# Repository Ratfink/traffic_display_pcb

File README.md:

# traffic_display_pcb
PCB for the Traffic Signal LED Matrix Display.

## Licensing
This work is licensed under the Creative Commons Attribution-ShareAlike 4.0
International License. To view a copy of this license, visit
http://creativecommons.org/licenses/by-sa/4.0/ or send a letter to Creative
Commons, PO Box 1866, Mountain View, CA 94042, USA.

Around half of the schematic is heavily based on the [Adafruit Feather ESP8266
HUZZAH](https://github.com/adafruit/Adafruit-Feather-ESP8266-HUZZAH-PCB).
Although Adafruit seems to have forgotten to include the exact version of the
Creative Commons Attribution-ShareAlike license used (at the time of writing),
and this project is not really a redistribution of theirs, I will include their
text as requested to try to avoid treading on any legal toes.

### Adafruit-Feather-ESP8266-HUZZAH-PCB

PCB files for the Adafruit Feather ESP8266 HUZZAH

Format is EagleCAD schematic and board layout

For more details, check out the product page at

* https://www.adafruit.com/product/2821

Adafruit invests time and resources providing this open source design, please
support Adafruit and open-source hardware by purchasing products from Adafruit!

Designed by Adafruit Industries.  
Creative Commons Attribution, Share-Alike license, check license.txt for more
information All text above must be included in any redistribution

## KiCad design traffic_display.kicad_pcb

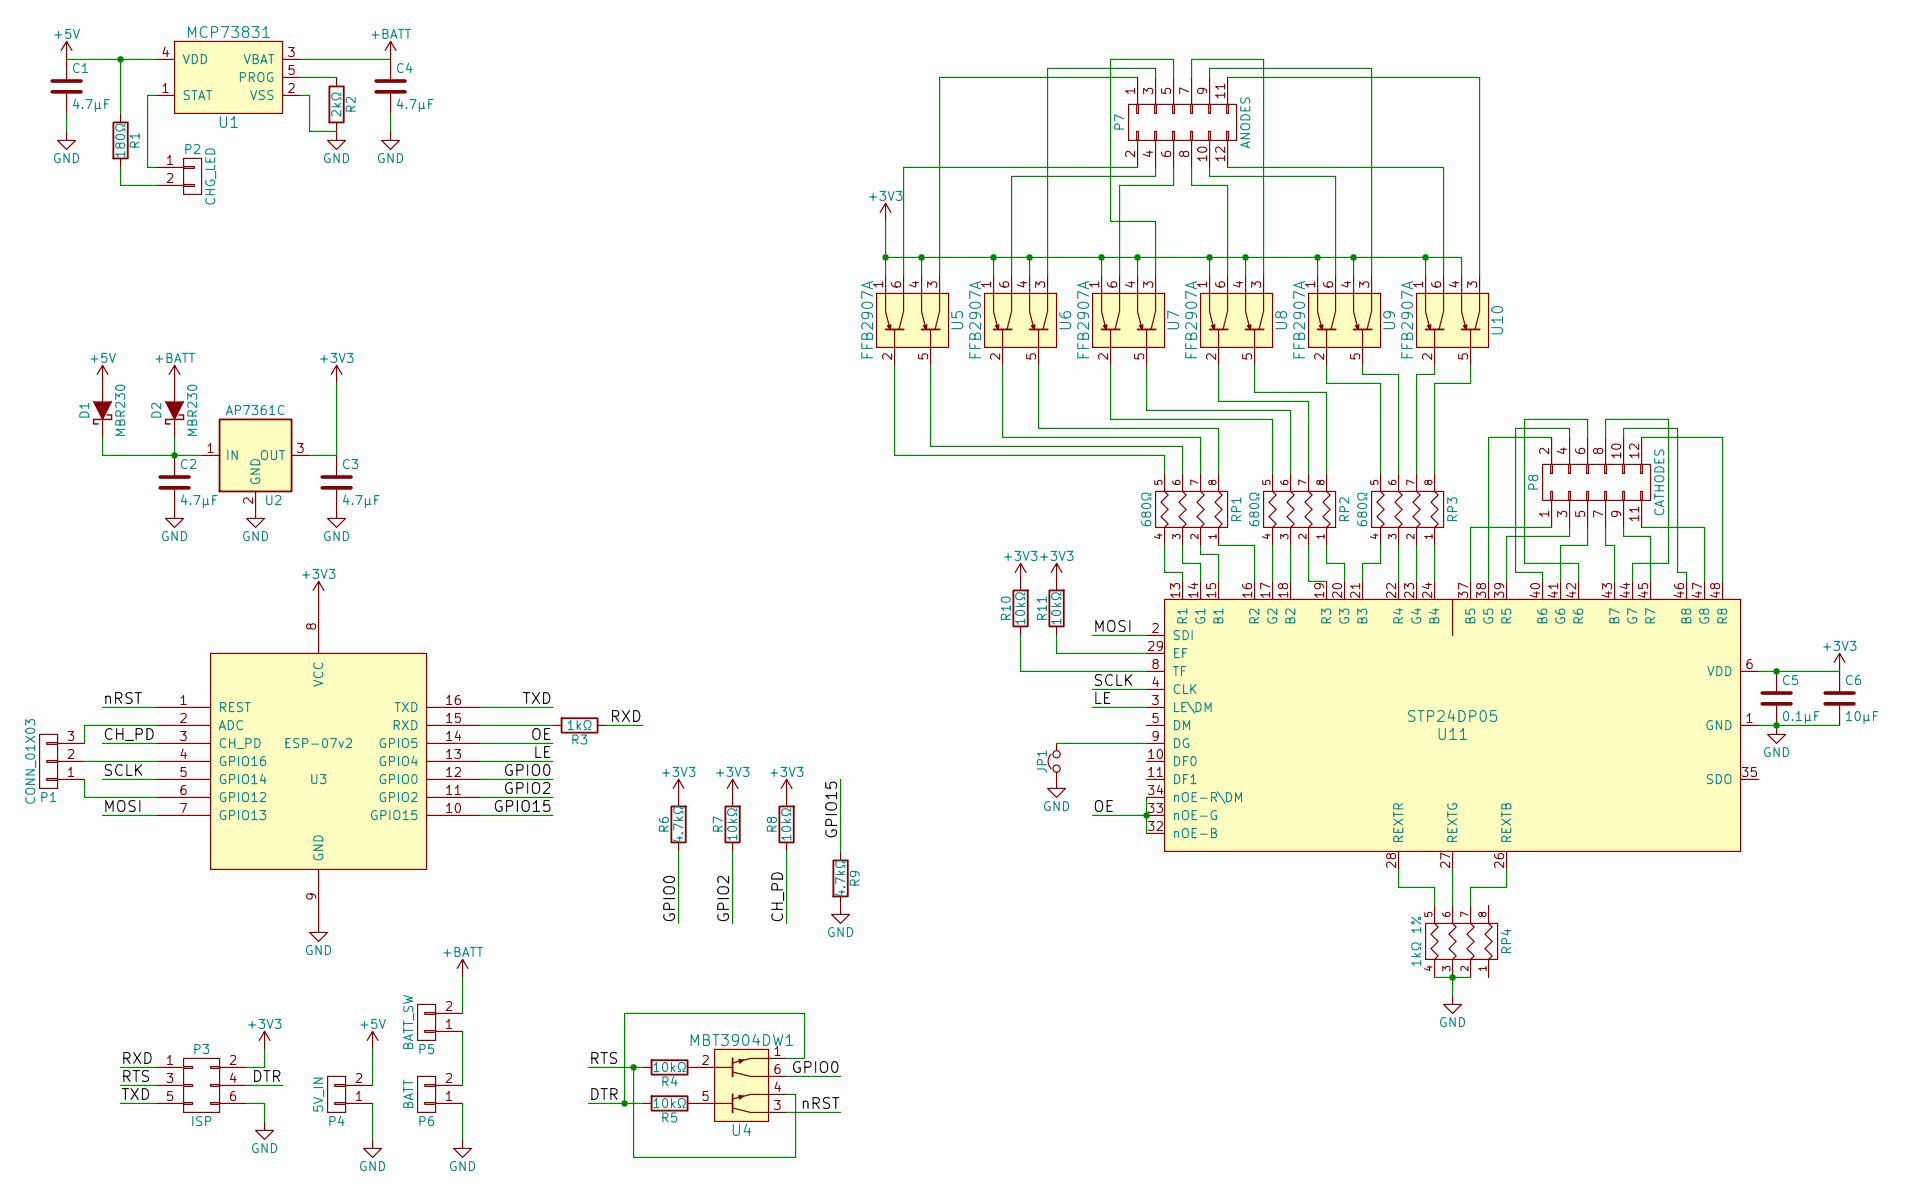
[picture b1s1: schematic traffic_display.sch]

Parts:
C1, C2, C3, C4: 4.7µF; C_0805_HandSoldering
C5: 0.1µF; C_0805_HandSoldering
C6: 10µF; C_0805_HandSoldering
D1, D2: MBR230; SOD-123
JP1: Jumper_NC_Small; R_0805_HandSoldering
P1: CONN_01X03; Pin_Header_Straight_1x03
P2: CHG_LED; Molex_KK-6410-02_02x2.54mm_Straight
P3: ISP; Pin_Header_Straight_2x03
P4: 5V_IN; Molex_KK-6410-02_02x2.54mm_Straight
P5: BATT_SW; Molex_KK-6410-02_02x2.54mm_Straight
P6: BATT; Molex_KK-6410-02_02x2.54mm_Straight
P7: ANODES; Pin_Header_Straight_2x06
P8: CATHODES; Pin_Header_Straight_2x06
R1: 180Ω; R_0805_HandSoldering
R2: 2kΩ; R_0805_HandSoldering
R3: 1kΩ; R_0805_HandSoldering
R4, R5, R7, R8, R10, R11: 10kΩ; R_0805_HandSoldering
R6, R9: 4.7kΩ; R_0805_HandSoldering
RP1, RP2, RP3: 680Ω; R_Array_Concave_4x0603
RP4: 1kΩ 1%; R_Array_Concave_4x0603
U1: MCP73831; SOT-23-5
U2: AP7361C; SOT-223
U3: ESP-07v2
U4: MBT3904DW1; SC-70-6_Handsoldering
U5, U6, U7, U8, U9, U10: FFB2907A; SC-70-6_Handsoldering
U11: STP24DP05; TQFP-48-1EP_7x7mm_Pitch0.5mm

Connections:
+3V3: C3.1, C5.1, C6.1, P3.2, R6.2, R7.2, R8.2, R10.2, R11.2, U2.3 (OUT), U3.8 (VCC), U5.1 (E1), U5.4 (E2), U6.1 (E1), U6.4 (E2), U7.1 (E1), U7.4 (E2), U8.1 (E1), U8.4 (E2), U9.1 (E1), U9.4 (E2), U10.1 (E1), U10.4 (E2), U11.6 (VDD), U11.31 (VDD)
+5V: C1.1, D1.2 (A), P4.2, R1.1, U1.4 (VDD)
+BATT: C4.1, D2.2 (A), P5.2, U1.3 (VBAT)
/CH_PD: R8.1, U3.3 (CH_PD)
/DTR: P3.4, R5.2, U4.1 (E1)
/GPIO0: R6.1, U3.12 (GPIO0), U4.6 (C1)
/GPIO2: R7.1, U3.11 (GPIO2)
/GPIO15: R9.1, U3.10 (GPIO15)
/LE: U3.13 (GPIO4), U11.3 (LE\DM)
/MOSI: U3.7 (GPIO13), U11.2 (SDI)
/OE: U3.14 (GPIO5), U11.32 (nOE-B), U11.33 (nOE-G), U11.34 (nOE-R\DM)
/RTS: P3.3, R4.2, U4.4 (E2)
/RXD: P3.1, R3.1
/SCLK: U3.5 (GPIO14), U11.4 (CLK)
/TXD: P3.5, U3.16 (TXD)
/nRST: U3.1 (REST), U4.3 (C2)
GND: C1.2, C2.2, C3.2, C4.2, C5.2, C6.2, JP1.1, P3.6, P4.1, P6.1, R2.2, R9.2, RP4.2, RP4.3, RP4.4, U1.2 (VSS), U2.2 (GND), U3.9 (GND), U11.1 (GND), U11.7 (GND), U11.12 (GND), U11.25 (GND), U11.30 (GND), U11.36 (GND), U11.49 (GND)
unnamed: C2.1, D1.1 (K), D2.1 (K), U2.1 (IN)
unnamed: JP1.2, U11.9 (DG)
unnamed: P1.1, U3.6 (GPIO12)
unnamed: P1.2, U3.4 (GPIO16)
unnamed: P1.3, U3.2 (ADC)
unnamed: P2.1, U1.1 (STAT)
unnamed: P2.2, R1.2
unnamed: P5.1, P6.2
unnamed: P7.1, U5.3 (C2)
unnamed: P7.2, U5.6 (C1)
unnamed: P7.3, U6.3 (C2)
unnamed: P7.4, U6.6 (C1)
unnamed: P7.5, U7.3 (C2)
unnamed: P7.6, U7.6 (C1)
unnamed: P7.7, U8.3 (C2)
unnamed: P7.8, U8.6 (C1)
unnamed: P7.9, U9.3 (C2)
unnamed: P7.10, U9.6 (C1)
unnamed: P7.11, U10.3 (C2)
unnamed: P7.12, U10.6 (C1)
unnamed: P8.1, U11.37 (B5)
unnamed: P8.2, U11.38 (G5)
unnamed: P8.3, U11.39 (R5)
unnamed: P8.4, U11.40 (B6)
unnamed: P8.5, U11.41 (G6)
unnamed: P8.6, U11.42 (R6)
unnamed: P8.7, U11.43 (B7)
unnamed: P8.8, U11.44 (G7)
unnamed: P8.9, U11.45 (R7)
unnamed: P8.10, U11.46 (B8)
unnamed: P8.11, U11.47 (G8)
unnamed: P8.12, U11.48 (R8)
unnamed: R2.1, U1.5 (PROG)
unnamed: R3.2, U3.15 (RXD)
unnamed: R4.1, U4.2 (B1)
unnamed: R5.1, U4.5 (B2)
unnamed: R10.1, U11.8 (TF)
unnamed: R11.1, U11.29 (EF)
unnamed: RP1.1, U11.16 (R2)
unnamed: RP1.2, U11.15 (B1)
unnamed: RP1.3, U11.14 (G1)
unnamed: RP1.4, U11.13 (R1)
unnamed: RP1.5 (R4), U5.2 (B1)
unnamed: RP1.6 (R3), U5.5 (B2)
unnamed: RP1.7 (R2), U6.2 (B1)
unnamed: RP1.8 (R1), U6.5 (B2)
unnamed: RP2.1, U11.20 (G3)
unnamed: RP2.2, U11.19 (R3)
unnamed: RP2.3, U11.18 (B2)
unnamed: RP2.4, U11.17 (G2)
unnamed: RP2.5 (R4), U7.2 (B1)
unnamed: RP2.6 (R3), U7.5 (B2)
unnamed: RP2.7 (R2), U8.2 (B1)
unnamed: RP2.8 (R1), U8.5 (B2)
unnamed: RP3.1, U11.24 (B4)
unnamed: RP3.2, U11.23 (G4)
unnamed: RP3.3, U11.22 (R4)
unnamed: RP3.4, U11.21 (B3)
unnamed: RP3.5 (R4), U9.2 (B1)
unnamed: RP3.6 (R3), U9.5 (B2)
unnamed: RP3.7 (R2), U10.2 (B1)
unnamed: RP3.8 (R1), U10.5 (B2)
unnamed: RP4.5 (R4), U11.28 (REXTR)
unnamed: RP4.6 (R3), U11.27 (REXTG)
unnamed: RP4.7 (R2), U11.26 (REXTB)

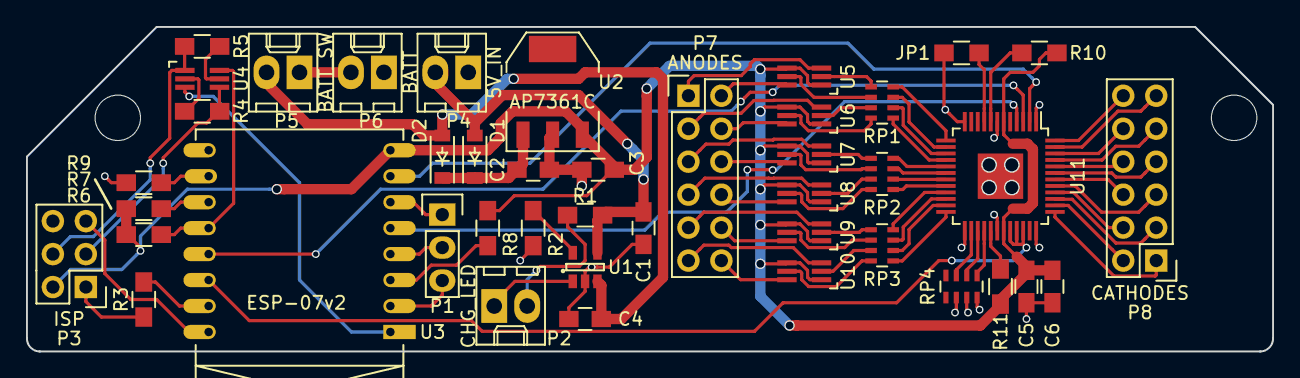
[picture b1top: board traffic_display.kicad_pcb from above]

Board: 2 copper layers, 96.0 x 25.0 mm, 43 parts (0 on the bottom side), 82 nets.

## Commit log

2016-08-13 Added initial schematic and PCB
2016-08-15 Make absolutely sure I'm complying with licenses
    Well, okay, it's hard to be absolutely sure when Adafruit forgot to
    include exact licensing information, but I'm pretty confident they won't
    try to send me to the slammer now.
